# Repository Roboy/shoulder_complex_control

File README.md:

# shoulder_complex_control
pcbs and code for controlling the shoulder complex platform

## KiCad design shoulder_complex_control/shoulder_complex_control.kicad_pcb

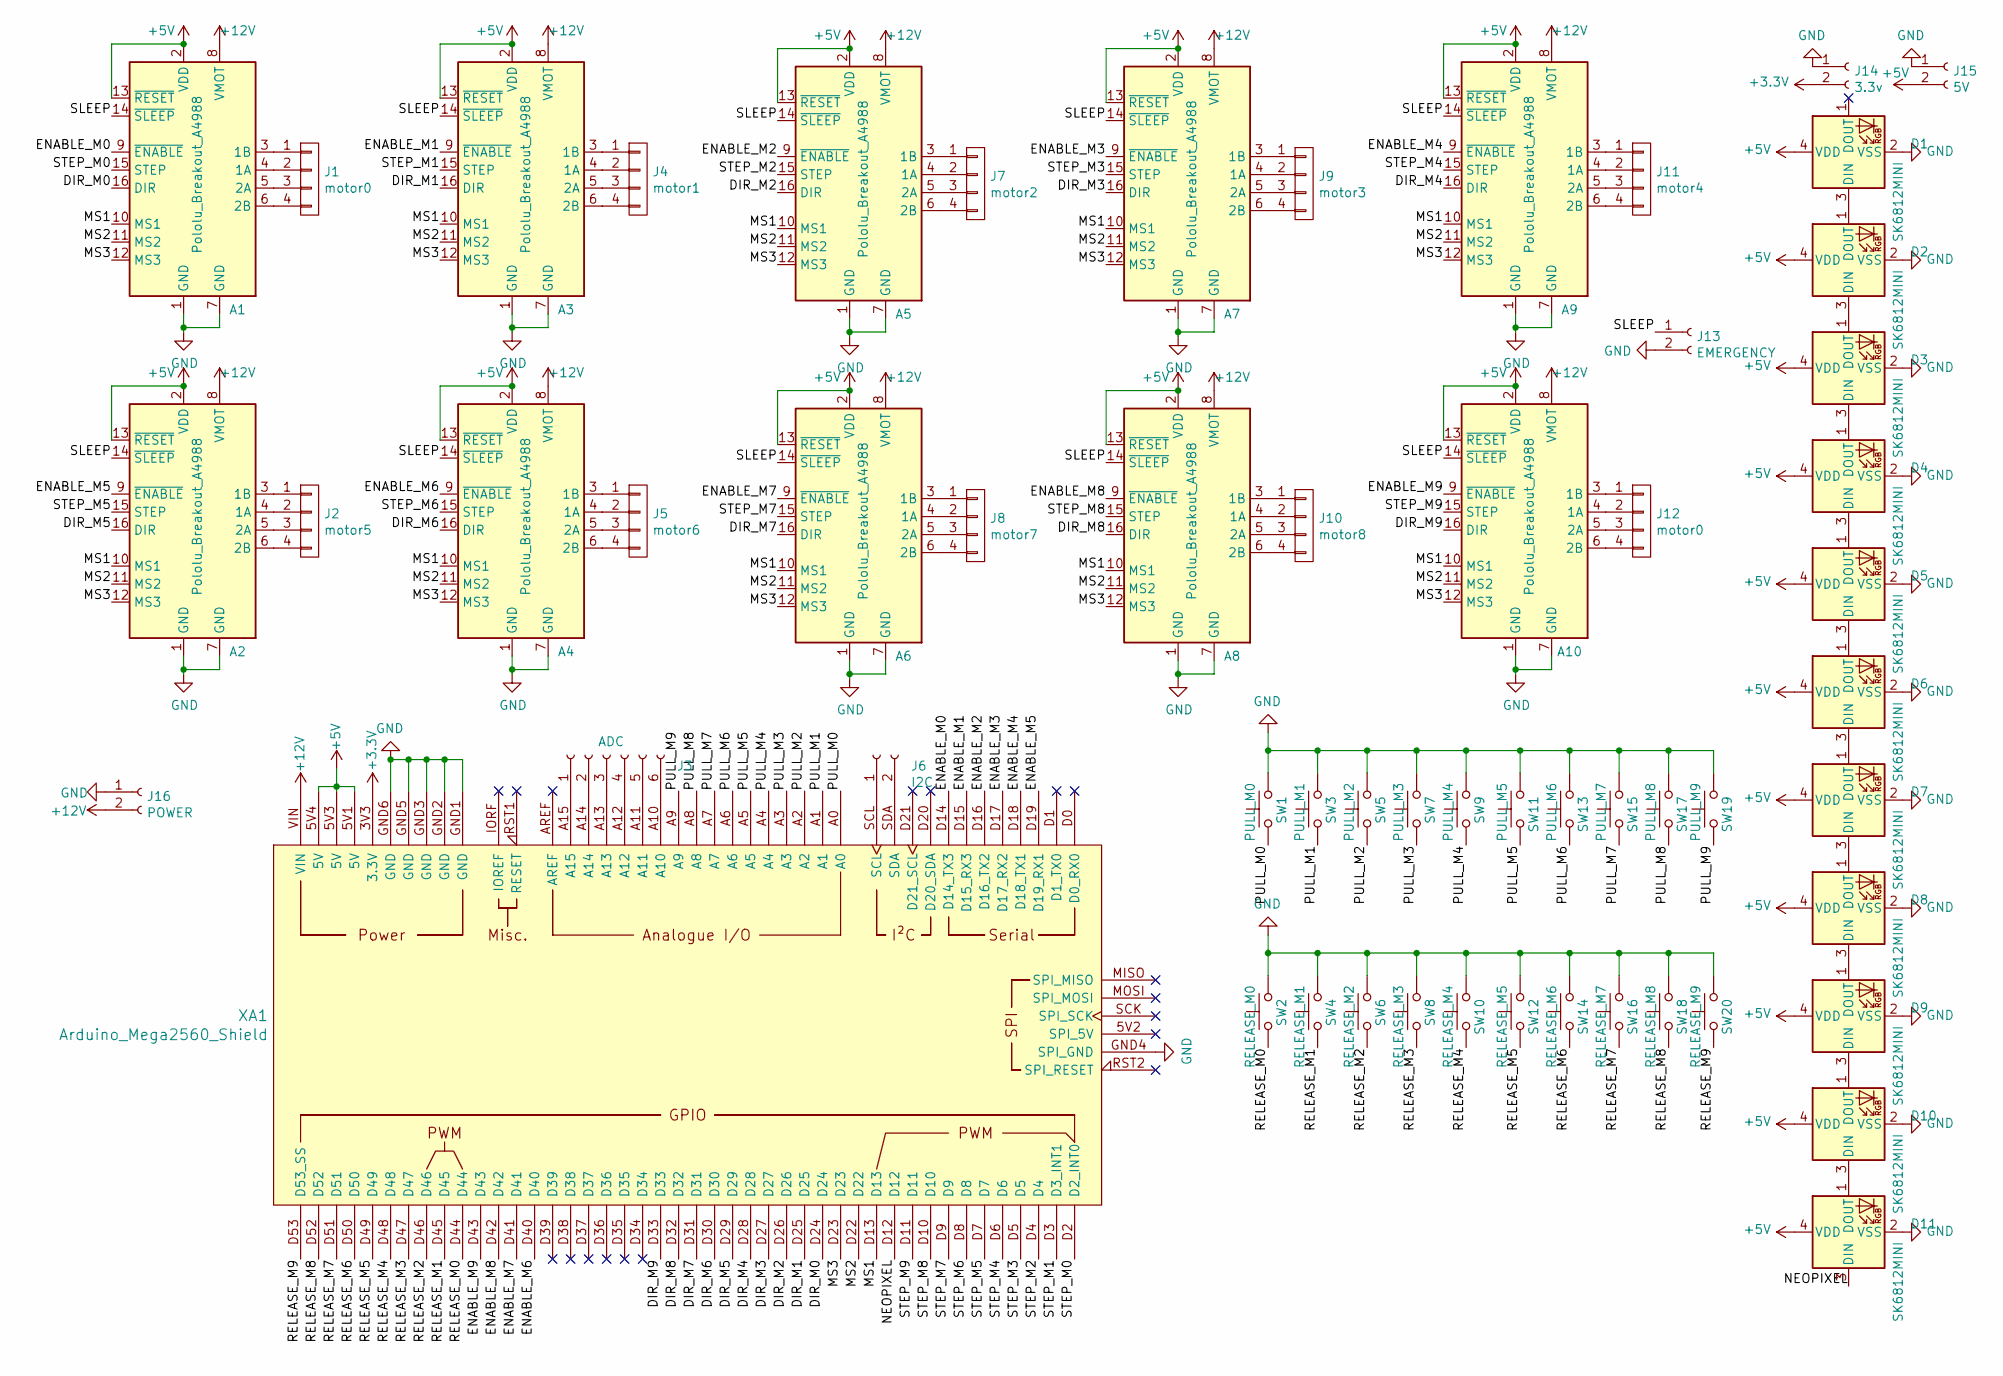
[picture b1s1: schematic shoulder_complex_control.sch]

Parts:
A1, A2, A3, A4, A5, A6, A7, A8, A9, A10: Pololu_Breakout_A4988; Pololu_Breakout-16_15.2x20.3mm
D1, D2, D3, D4, D5, D6, D7, D8, D9, D10, D11: SK6812MINI; LED_SK6812MINI_PLCC4_3.5x3.5mm_P1.75mm
J1, J12: motor0; TE-Connectivity_Micro-Match_connector_02x02_Pitch_1.27mm
J2: motor5; TE-Connectivity_Micro-Match_connector_02x02_Pitch_1.27mm
J3: ADC; TE-Connectivity_Micro-Match_connector_02x03_Pitch_1.27mm
J4: motor1; TE-Connectivity_Micro-Match_connector_02x02_Pitch_1.27mm
J5: motor6; TE-Connectivity_Micro-Match_connector_02x02_Pitch_1.27mm
J6: I2C; PinSocket_1x02_P2.54mm_Vertical
J7: motor2; TE-Connectivity_Micro-Match_connector_02x02_Pitch_1.27mm
J8: motor7; TE-Connectivity_Micro-Match_connector_02x02_Pitch_1.27mm
J9: motor3; TE-Connectivity_Micro-Match_connector_02x02_Pitch_1.27mm
J10: motor8; TE-Connectivity_Micro-Match_connector_02x02_Pitch_1.27mm
J11: motor4; TE-Connectivity_Micro-Match_connector_02x02_Pitch_1.27mm
J13: EMERGENCY; PinSocket_1x02_P2.54mm_Vertical
J14: 3.3v; PinSocket_1x02_P2.54mm_Vertical
J15: 5V; PinSocket_1x02_P2.54mm_Vertical
J16: POWER; Wago_2060_2_SMD
SW1: PULL_M0; PinSocket_1x02_P2.54mm_Vertical
SW2: RELEASE_M0; PinSocket_1x02_P2.54mm_Vertical
SW3: PULL_M1; PinSocket_1x02_P2.54mm_Vertical
SW4: RELEASE_M1; PinSocket_1x02_P2.54mm_Vertical
SW5: PULL_M2; PinSocket_1x02_P2.54mm_Vertical
SW6: RELEASE_M2; PinSocket_1x02_P2.54mm_Vertical
SW7: PULL_M3; PinSocket_1x02_P2.54mm_Vertical
SW8: RELEASE_M3; PinSocket_1x02_P2.54mm_Vertical
SW9: PULL_M4; PinSocket_1x02_P2.54mm_Vertical
SW10: RELEASE_M4; PinSocket_1x02_P2.54mm_Vertical
SW11: PULL_M5; PinSocket_1x02_P2.54mm_Vertical
SW12: RELEASE_M5; PinSocket_1x02_P2.54mm_Vertical
SW13: PULL_M6; PinSocket_1x02_P2.54mm_Vertical
SW14: RELEASE_M6; PinSocket_1x02_P2.54mm_Vertical
SW15: PULL_M7; PinSocket_1x02_P2.54mm_Vertical
SW16: RELEASE_M7; PinSocket_1x02_P2.54mm_Vertical
SW17: PULL_M8; PinSocket_1x02_P2.54mm_Vertical
SW18: RELEASE_M8; PinSocket_1x02_P2.54mm_Vertical
SW19: PULL_M9; PinSocket_1x02_P2.54mm_Vertical
SW20: RELEASE_M9; PinSocket_1x02_P2.54mm_Vertical
XA1: Arduino_Mega2560_Shield

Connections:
+3V3: J14.2, XA1.3V3 (3.3V)
+5V: A1.2 (VDD), A1.13 (~RESET), A2.2 (VDD), A2.13 (~RESET), A3.2 (VDD), A3.13 (~RESET), A4.2 (VDD), A4.13 (~RESET), A5.2 (VDD), A5.13 (~RESET), A6.2 (VDD), A6.13 (~RESET), A7.2 (VDD), A7.13 (~RESET), A8.2 (VDD), A8.13 (~RESET), A9.2 (VDD), A9.13 (~RESET), A10.2 (VDD), A10.13 (~RESET), D1.4 (VDD), D2.4 (VDD), D3.4 (VDD), D4.4 (VDD), D5.4 (VDD), D6.4 (VDD), D7.4 (VDD), D8.4 (VDD), D9.4 (VDD), D10.4 (VDD), D11.4 (VDD), J15.2, XA1.5V1 (5V), XA1.5V3 (5V), XA1.5V4 (5V)
+12V: A1.8 (VMOT), A2.8 (VMOT), A3.8 (VMOT), A4.8 (VMOT), A5.8 (VMOT), A6.8 (VMOT), A7.8 (VMOT), A8.8 (VMOT), A9.8 (VMOT), A10.8 (VMOT), J16.2, XA1.VIN
/DIR_M0: A1.16 (DIR), XA1.D24
/DIR_M1: A3.16 (DIR), XA1.D25
/DIR_M2: A5.16 (DIR), XA1.D26
/DIR_M3: A7.16 (DIR), XA1.D27
/DIR_M4: A9.16 (DIR), XA1.D28
/DIR_M5: A2.16 (DIR), XA1.D29
/DIR_M6: A4.16 (DIR), XA1.D30
/DIR_M7: A6.16 (DIR), XA1.D31
/DIR_M8: A8.16 (DIR), XA1.D32
/DIR_M9: A10.16 (DIR), XA1.D33
/ENABLE_M0: A1.9 (~ENABLE), XA1.D14 (D14_TX3)
/ENABLE_M1: A3.9 (~ENABLE), XA1.D15 (D15_RX3)
/ENABLE_M2: A5.9 (~ENABLE), XA1.D16 (D16_TX2)
/ENABLE_M3: A7.9 (~ENABLE), XA1.D17 (D17_RX2)
/ENABLE_M4: A9.9 (~ENABLE), XA1.D18 (D18_TX1)
/ENABLE_M5: A2.9 (~ENABLE), XA1.D19 (D19_RX1)
/ENABLE_M6: A4.9 (~ENABLE), XA1.D40
/ENABLE_M7: A6.9 (~ENABLE), XA1.D41
/ENABLE_M8: A8.9 (~ENABLE), XA1.D42
/ENABLE_M9: A10.9 (~ENABLE), XA1.D43
/MS1: A1.10 (MS1), A2.10 (MS1), A3.10 (MS1), A4.10 (MS1), A5.10 (MS1), A6.10 (MS1), A7.10 (MS1), A8.10 (MS1), A9.10 (MS1), A10.10 (MS1), XA1.D13
/MS2: A1.11 (MS2), A2.11 (MS2), A3.11 (MS2), A4.11 (MS2), A5.11 (MS2), A6.11 (MS2), A7.11 (MS2), A8.11 (MS2), A9.11 (MS2), A10.11 (MS2), XA1.D22
/MS3: A1.12 (MS3), A2.12 (MS3), A3.12 (MS3), A4.12 (MS3), A5.12 (MS3), A6.12 (MS3), A7.12 (MS3), A8.12 (MS3), A9.12 (MS3), A10.12 (MS3), XA1.D23
/NEOPIXEL: D11.3 (DIN), XA1.D12
/PULL_M0: SW1.1, XA1.A0
/PULL_M1: SW3.1, XA1.A1
/PULL_M2: SW5.1, XA1.A2
/PULL_M3: SW7.1, XA1.A3
/PULL_M4: SW9.1, XA1.A4
/PULL_M5: SW11.1, XA1.A5
/PULL_M6: SW13.1, XA1.A6
/PULL_M7: SW15.1, XA1.A7
/PULL_M8: SW17.1, XA1.A8
/PULL_M9: SW19.1, XA1.A9
/RELEASE_M0: SW2.1, XA1.D44
/RELEASE_M1: SW4.1, XA1.D45
/RELEASE_M2: SW6.1, XA1.D46
/RELEASE_M3: SW8.1, XA1.D47
/RELEASE_M4: SW10.1, XA1.D48
/RELEASE_M5: SW12.1, XA1.D49
/RELEASE_M6: SW14.1, XA1.D50
/RELEASE_M7: SW16.1, XA1.D51
/RELEASE_M8: SW18.1, XA1.D52
/RELEASE_M9: SW20.1, XA1.D53 (D53_SS)
/SLEEP: A1.14 (~SLEEP), A2.14 (~SLEEP), A3.14 (~SLEEP), A4.14 (~SLEEP), A5.14 (~SLEEP), A6.14 (~SLEEP), A7.14 (~SLEEP), A8.14 (~SLEEP), A9.14 (~SLEEP), A10.14 (~SLEEP), J13.1
/STEP_M0: A1.15 (STEP), XA1.D2 (D2_INT0)
/STEP_M1: A3.15 (STEP), XA1.D3 (D3_INT1)
/STEP_M2: A5.15 (STEP), XA1.D4
/STEP_M3: A7.15 (STEP), XA1.D5
/STEP_M4: A9.15 (STEP), XA1.D6
/STEP_M5: A2.15 (STEP), XA1.D7
/STEP_M6: A4.15 (STEP), XA1.D8
/STEP_M7: A6.15 (STEP), XA1.D9
/STEP_M8: A8.15 (STEP), XA1.D10
/STEP_M9: A10.15 (STEP), XA1.D11
GND: A1.1 (GND), A1.7 (GND), A2.1 (GND), A2.7 (GND), A3.1 (GND), A3.7 (GND), A4.1 (GND), A4.7 (GND), A5.1 (GND), A5.7 (GND), A6.1 (GND), A6.7 (GND), A7.1 (GND), A7.7 (GND), A8.1 (GND), A8.7 (GND), A9.1 (GND), A9.7 (GND), A10.1 (GND), A10.7 (GND), D1.2 (VSS), D2.2 (VSS), D3.2 (VSS), D4.2 (VSS), D5.2 (VSS), D6.2 (VSS), D7.2 (VSS), D8.2 (VSS), D9.2 (VSS), D10.2 (VSS), D11.2 (VSS), J13.2, J14.1, J15.1, J16.1, SW1.2, SW2.2, SW3.2, SW4.2, SW5.2, SW6.2, SW7.2, SW8.2, SW9.2, SW10.2, SW11.2, SW12.2, SW13.2, SW14.2, SW15.2, SW16.2, SW17.2, SW18.2, SW19.2, SW20.2, XA1.GND1 (GND), XA1.GND2 (GND), XA1.GND3 (GND), XA1.GND4 (SPI_GND), XA1.GND5 (GND), XA1.GND6 (GND)
unnamed: A1.3 (1B), J1.1
unnamed: A1.4 (1A), J1.2
unnamed: A1.5 (2A), J1.3
unnamed: A1.6 (2B), J1.4
unnamed: A2.3 (1B), J2.1
unnamed: A2.4 (1A), J2.2
unnamed: A2.5 (2A), J2.3
unnamed: A2.6 (2B), J2.4
unnamed: A3.3 (1B), J4.1
unnamed: A3.4 (1A), J4.2
unnamed: A3.5 (2A), J4.3
unnamed: A3.6 (2B), J4.4
unnamed: A4.3 (1B), J5.1
unnamed: A4.4 (1A), J5.2
unnamed: A4.5 (2A), J5.3
unnamed: A4.6 (2B), J5.4
unnamed: A5.3 (1B), J7.1
unnamed: A5.4 (1A), J7.2
unnamed: A5.5 (2A), J7.3
unnamed: A5.6 (2B), J7.4
unnamed: A6.3 (1B), J8.1
unnamed: A6.4 (1A), J8.2
unnamed: A6.5 (2A), J8.3
unnamed: A6.6 (2B), J8.4
unnamed: A7.3 (1B), J9.1
unnamed: A7.4 (1A), J9.2
unnamed: A7.5 (2A), J9.3
unnamed: A7.6 (2B), J9.4
unnamed: A8.3 (1B), J10.1
unnamed: A8.4 (1A), J10.2
unnamed: A8.5 (2A), J10.3
unnamed: A8.6 (2B), J10.4
unnamed: A9.3 (1B), J11.1
unnamed: A9.4 (1A), J11.2
unnamed: A9.5 (2A), J11.3
unnamed: A9.6 (2B), J11.4
unnamed: A10.3 (1B), J12.1
unnamed: A10.4 (1A), J12.2
unnamed: A10.5 (2A), J12.3
unnamed: A10.6 (2B), J12.4
unnamed: D1.3 (DIN), D2.1 (DOUT)
unnamed: D2.3 (DIN), D3.1 (DOUT)
unnamed: D3.3 (DIN), D4.1 (DOUT)
unnamed: D4.3 (DIN), D5.1 (DOUT)
unnamed: D5.3 (DIN), D6.1 (DOUT)
unnamed: D6.3 (DIN), D7.1 (DOUT)
unnamed: D7.3 (DIN), D8.1 (DOUT)
unnamed: D8.3 (DIN), D9.1 (DOUT)
unnamed: D9.3 (DIN), D10.1 (DOUT)
unnamed: D10.3 (DIN), D11.1 (DOUT)
unnamed: J3.1, XA1.A15
unnamed: J3.2, XA1.A14
unnamed: J3.3, XA1.A13
unnamed: J3.4, XA1.A12
unnamed: J3.5, XA1.A11
unnamed: J3.6, XA1.A10
unnamed: J6.1, XA1.SCL
unnamed: J6.2, XA1.SDA

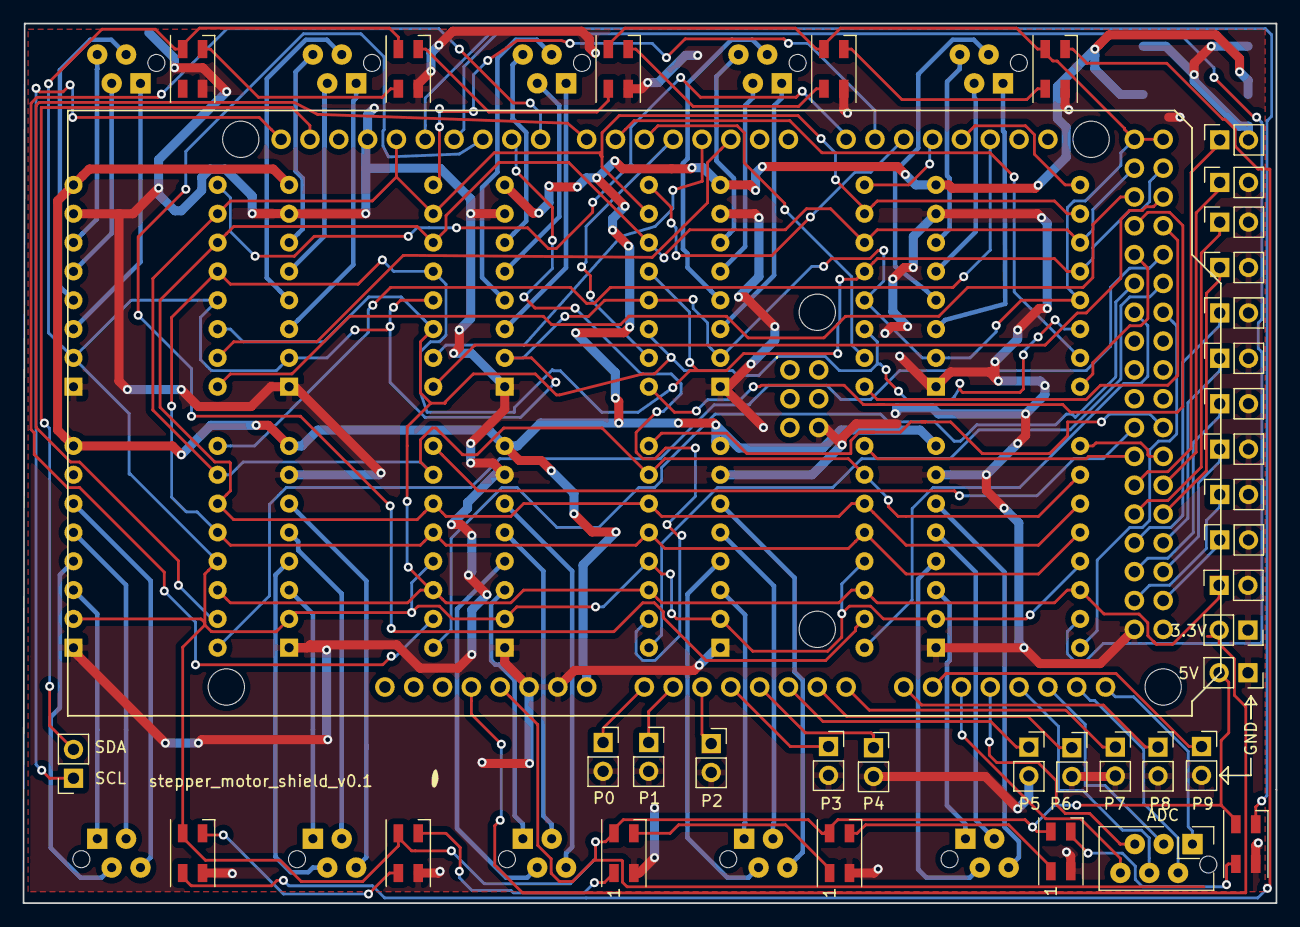
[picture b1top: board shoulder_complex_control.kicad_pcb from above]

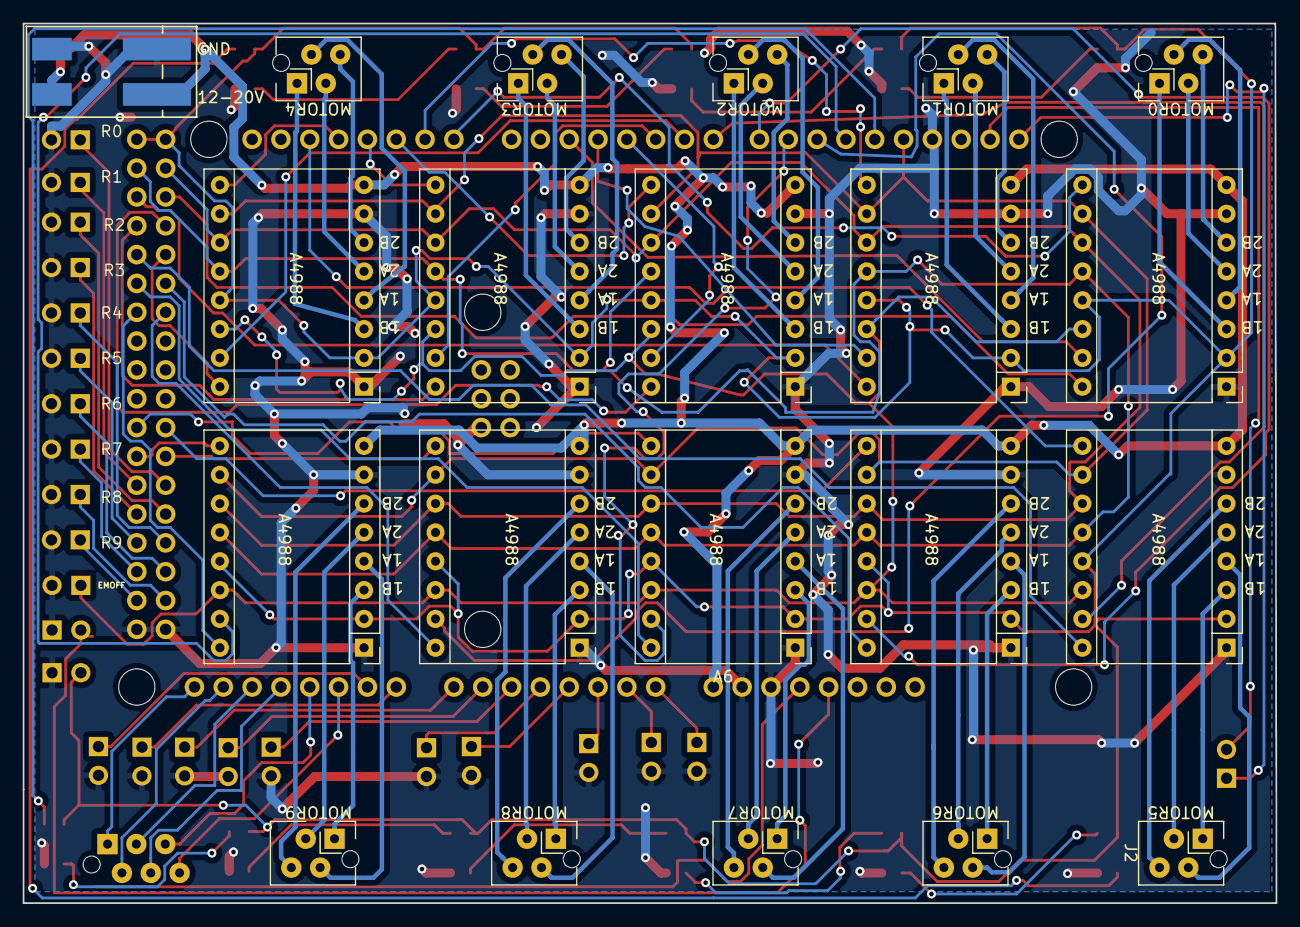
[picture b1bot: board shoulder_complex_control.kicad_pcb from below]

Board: 2 copper layers, 110.4 x 77.5 mm, 58 parts (21 on the bottom side), 117 nets.

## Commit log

2019-06-26 layout almost done
2019-06-28 v0.1 ordered from aisler
